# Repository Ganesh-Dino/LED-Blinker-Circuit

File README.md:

# LED-Blinker-Circuit
Designed and simulated a 2-layer SMD-based LED Blinker circuit using NE555 timer in astable mode, complete with schematic capture, layout routing, and DRC-compliant PCB design using KiCad.

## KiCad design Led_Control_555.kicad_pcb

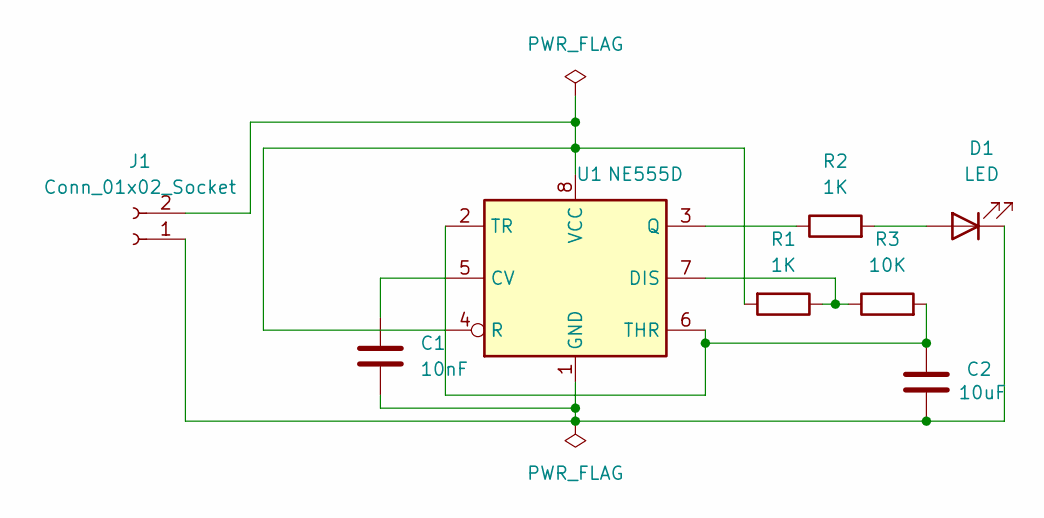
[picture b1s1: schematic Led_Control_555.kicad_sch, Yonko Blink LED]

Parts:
C1: 10nF; WCAP-CSGP_0603_R
C2: 10uF; CAPC2012X140N
D1: LED; LED_0402_1005Metric_Pad0.77x0.64mm_HandSolder
J1: Conn_01x02_Socket; JST_ACH_BM02B-ACHSS-GAN-ETF_1x02-1MP_P1.20mm_Vertical
R1, R2: 1K; CAPC1005X55N
R3: 10K; RESC1005X40N
U1: NE555D; SOIC-8_3.9x4.9mm_P1.27mm

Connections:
unnamed: D1.2 (A), R2.2
unnamed: C1.2, C2.2, D1.1 (K), J1.1, U1.1 (GND)
unnamed: J1.2, R1.2, U1.4 (R), U1.8 (VCC)
unnamed: C1.1, U1.5 (CV)
unnamed: R1.1, R3.1, U1.7 (DIS)
unnamed: R2.1, U1.3 (Q)
unnamed: C2.1, R3.2, U1.2 (TR), U1.6 (THR)

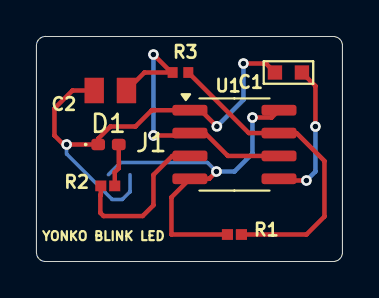
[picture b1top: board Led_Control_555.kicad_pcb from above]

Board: 2 copper layers, 17.0 x 12.5 mm, 8 parts (1 on the bottom side), 7 nets.
